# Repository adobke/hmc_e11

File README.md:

hmc_e11
=======

Code for Harvey Mudd's: E11: Autonomous Vehicles

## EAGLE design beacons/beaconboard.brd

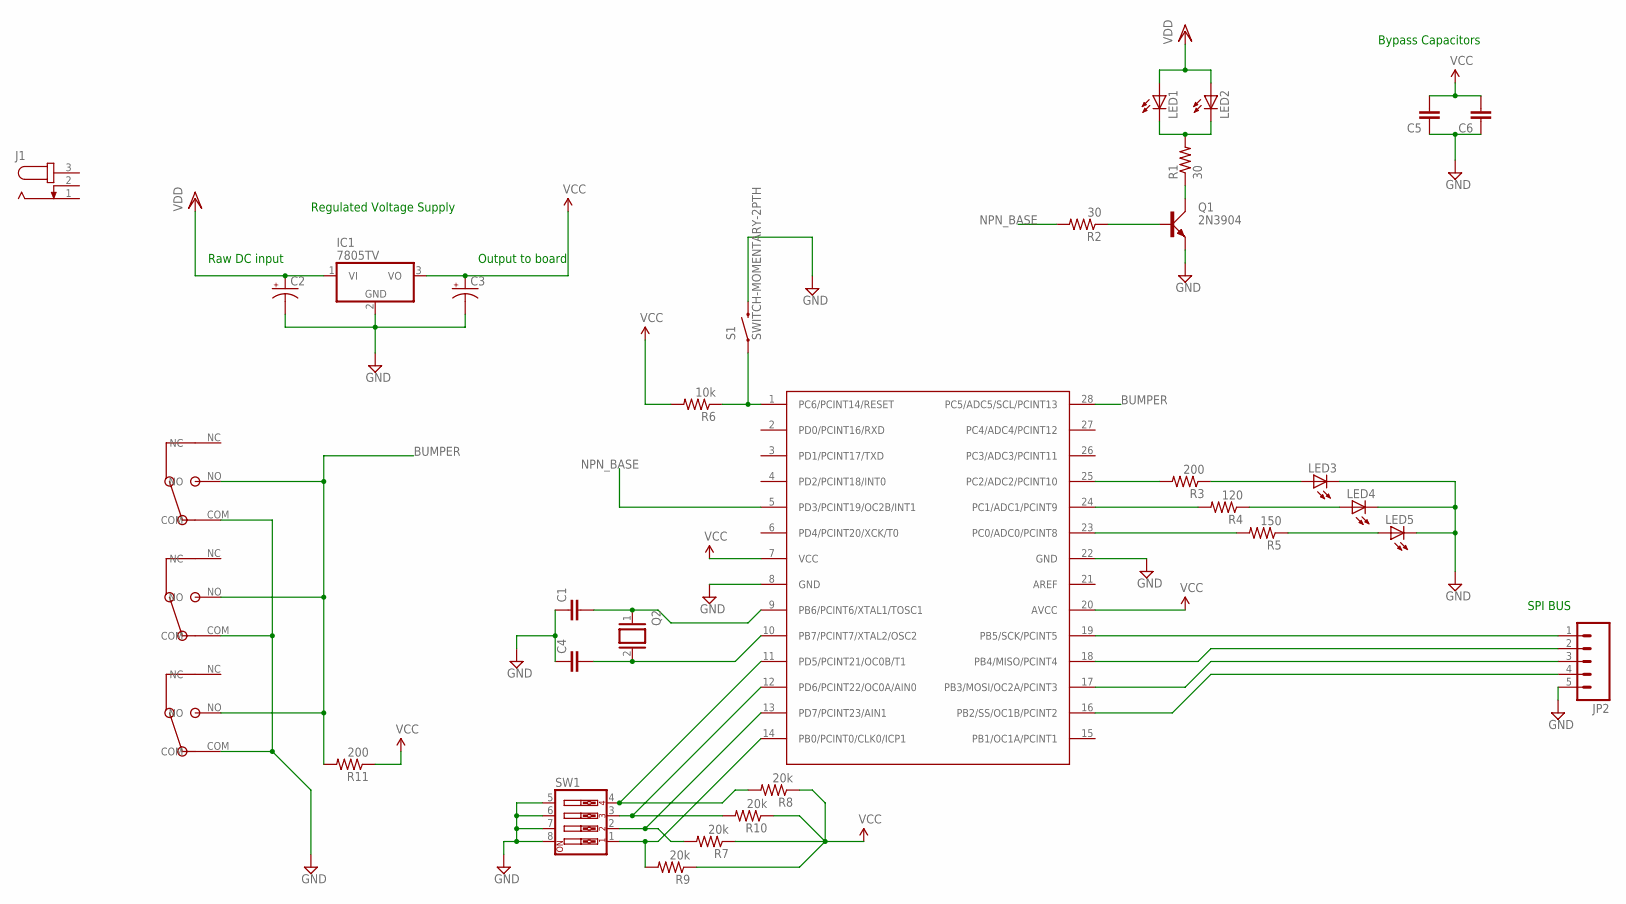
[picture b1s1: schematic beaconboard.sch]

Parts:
C1, C4, C5, C6: CAPPTH; CAP-PTH-SMALL
C2, C3: CAP_POLPTH2; CPOL-RADIAL-10UF-25V
IC1: 7805TV; TO220V
J1: JACK-PLUG1; SPC4078
JP2: M05LOCK_LONGPADS; 1X05_LOCK_LONGPADS
LED1, LED2: LED-2AC-CP41B-WES; CP41B
LED3, LED4, LED5: LED5MM
Q1: 2N3904; TO92D
Q2: XTAL/S; QS
R1, R2: 30; AXIAL-0.4
R3, R11: 200; AXIAL-0.4
R4: 120; AXIAL-0.4
R5: 150; AXIAL-0.4
R6: 10k; AXIAL-0.4
R7, R8, R9, R10: 20k; AXIAL-0.4
S1: SWITCH-MOMENTARY-2PTH; TACTILE-PTH
SW1: SW_DIP-4; EDG-04
U$1, U$2, U$3: DF2-L; D2F-L
U$4: ATMEGA328; DIL28-3

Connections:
BUMPER: R11.P$2 (2), U$1.NO, U$2.NO, U$3.NO, U$4.28 (PC5/ADC5/SCL/PCINT13)
GND: C1.1, C2.2 (-), C3.2 (-), C4.1, C5.1, C6.1, IC1.2 (GND), JP2.5, LED3.K (C), LED4.K (C), LED5.K (C), Q1.E, S1.3 (2), SW1.5, SW1.6, SW1.7, SW1.8, U$1.COM, U$2.COM, U$3.COM, U$4.8 (GND), U$4.22 (GND)
unnamed: Q1.C, R1.P$1 (1)
unnamed: Q1.B, R2.P$1 (1)
unnamed: LED1.1 (C), LED1.4 (C), LED2.1 (C), LED2.4 (C), R1.P$2 (2)
unnamed: R4.P$2 (2), U$4.24 (PC1/ADC1/PCINT9)
unnamed: JP2.1, U$4.19 (PB5/SCK/PCINT5)
unnamed: JP2.2, U$4.18 (PB4/MISO/PCINT4)
unnamed: JP2.3, U$4.17 (PB3/MOSI/OC2A/PCINT3)
unnamed: LED3.A, R3.P$1 (1)
unnamed: LED4.A, R4.P$1 (1)
unnamed: LED5.A, R5.P$1 (1)
unnamed: R6.P$1 (1), S1.1, U$4.1 (PC6/PCINT14/RESET)
unnamed: C1.2, Q2.1, U$4.9 (PB6/PCINT6/XTAL1/TOSC1)
unnamed: C4.2, Q2.2, U$4.10 (PB7/PCINT7/XTAL2/OSC2)
unnamed: R7.P$2 (2), SW1.2, U$4.13 (PD7/PCINT23/AIN1)
unnamed: R8.P$2 (2), SW1.4, U$4.11 (PD5/PCINT21/OC0B/T1)
unnamed: R10.P$2 (2), SW1.3, U$4.12 (PD6/PCINT22/OC0A/AIN0)
unnamed: R5.P$2 (2), U$4.23 (PC0/ADC0/PCINT8)
unnamed: R3.P$2 (2), U$4.25 (PC2/ADC2/PCINT10)
unnamed: R9.P$2 (2), SW1.1, U$4.14 (PB0/PCINT0/CLK0/ICP1)
unnamed: JP2.4, U$4.16 (PB2/SS/OC1B/PCINT2)
NPN_BASE: R2.P$2 (2), U$4.5 (PD3/PCINT19/OC2B/INT1)
VCC: C3.1 (+), C5.2, C6.2, IC1.3 (VO), R6.P$2 (2), R7.P$1 (1), R8.P$1 (1), R9.P$1 (1), R10.P$1 (1), R11.P$1 (1), U$4.7 (VCC), U$4.20 (AVCC)
VDD: C2.1 (+), IC1.1 (VI), LED1.2 (A), LED1.3 (A), LED2.2 (A), LED2.3 (A)

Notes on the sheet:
Output to board
Raw DC input
Bypass Capacitors
Regulated Voltage Supply
SPI BUS

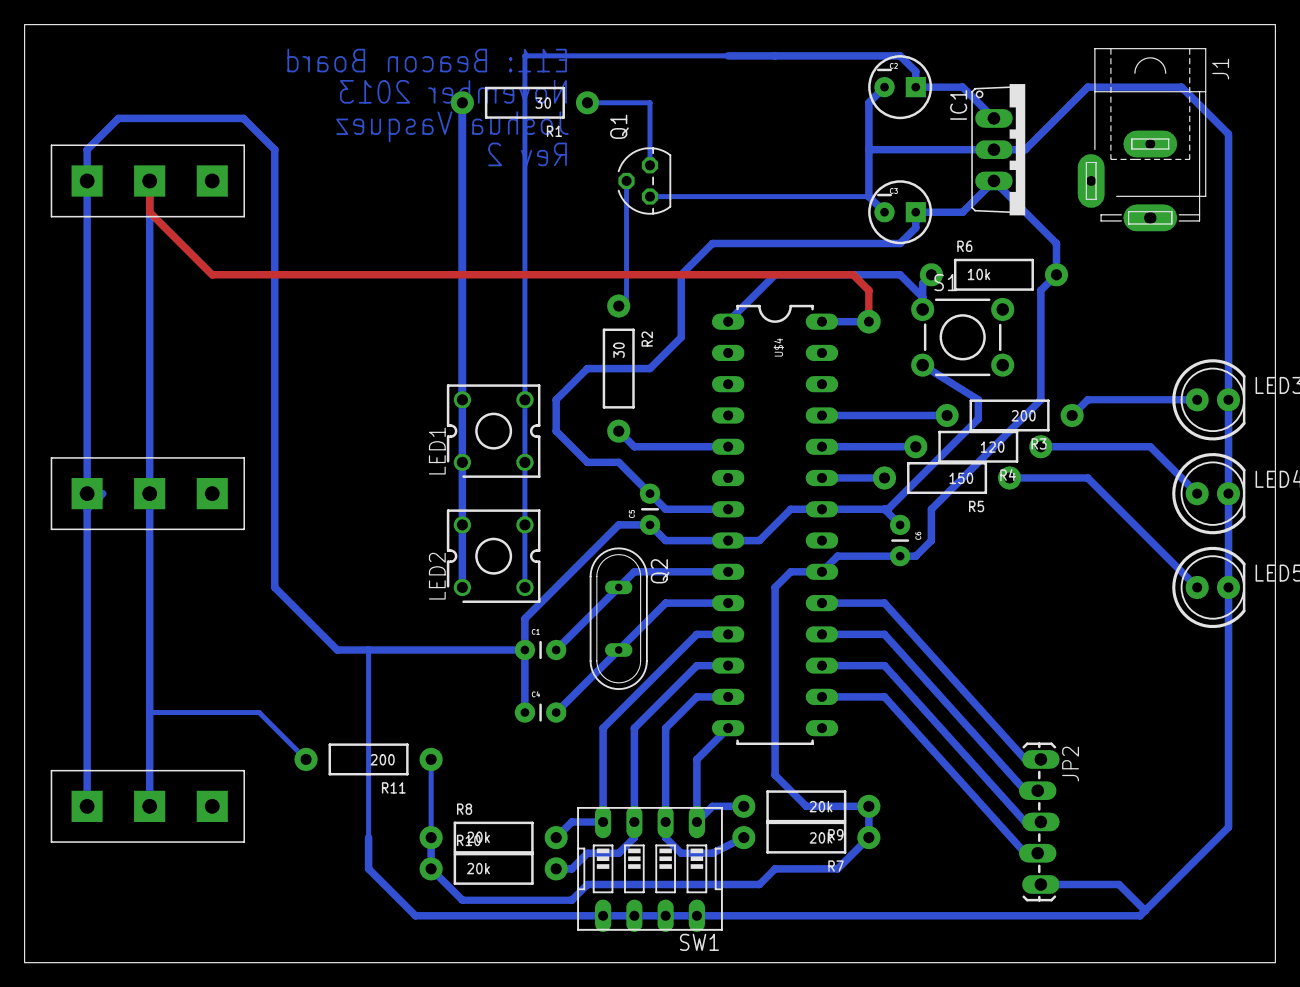
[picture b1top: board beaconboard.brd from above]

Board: 2 copper layers, 101.6 x 76.2 mm, 33 parts (0 on the bottom side), 25 nets.

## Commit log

2013-11-03 mostly finished with beacon board
2013-11-04 Add pull up resistor to bumpers
2013-11-04 Move leds above npn transistor
2013-11-04 Reroute for new transistor configuration
2013-11-04 Moving around files.. initial commit to GH
2013-11-04 separated spi/led connections
2013-11-04 deleted previous version of beaconboard.sch
2013-11-04 deleted previous version of beaconboard.brd
2013-11-04 added DC jack; fixed NPN base resistor val

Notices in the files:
parts and their libraries:
SparkFun-Capacitors: Licensing: CC v3.0 Share-Alike You are welcome to use this library for commercial purposes.
